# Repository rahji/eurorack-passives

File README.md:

# Passive Eurorack Non-Modules

These are small PCBs for a variety of passive Eurorack "non-modules." I designed them to be under 1" in at least one dimension¹, so they can fit neatly under a strip of 1.5" aluminum angle (architectural angle, .0625" thick) — which makes for a perfect extra row in my Halliburton cases. If you wanted to, you could probably make a 1u panel for each of them. Or put a few of them vertically behind a single 8hp 3u panel. Or put them in a mint tin. Or whatever.

The circuits are all pretty simple, use only through-hole components, and the PCBs are all essentially 1 layer². Some of them circuits are based on designs by other Eurorack folks (who likely were inspired by others). For examples, see [Yan's Patchpals](https://www.youtube.com/channel/UChDo3AJkkG8NR5XDoN58YQw), the [Doepfer A-100 DIY page](http://www.doepfer.de/DIY/a100_diy.htm), and [Synth Diy Guy](https://www.youtube.com/channel/UCaTca38SJErVLsfYkrg2R9w).

## Schematics

I've included PNG images of each of the schematics, because I hate when I find Eagle projects on GitHub and have to clone them (and open them in Eagle!) before I can get a glimpse of the schematic. 

## Assembly and BOMs

The silkscreens don't necessarily indicate which side of the board to place to the component. You can decide which side makes the most sense for you. Obviously make sure the polarity matches what the silkscreen says though.

## Panels

Labels and graphics are up to you, but I've included PDFs and AIs for each of the modules' holes. The AI files have separate layers for the hole dimensions, centered crosshairs, board dimensions, and name of the module. There's also a PDF of all of the panels on one page.

---

¹ The traces on the boards are all on the bottom layer, but practically it makes sense to have them fabricated as 2-layer boards. If you want to mill them as single-layer boards yourself, and you're willing to be creative with your soldering, you could do it.

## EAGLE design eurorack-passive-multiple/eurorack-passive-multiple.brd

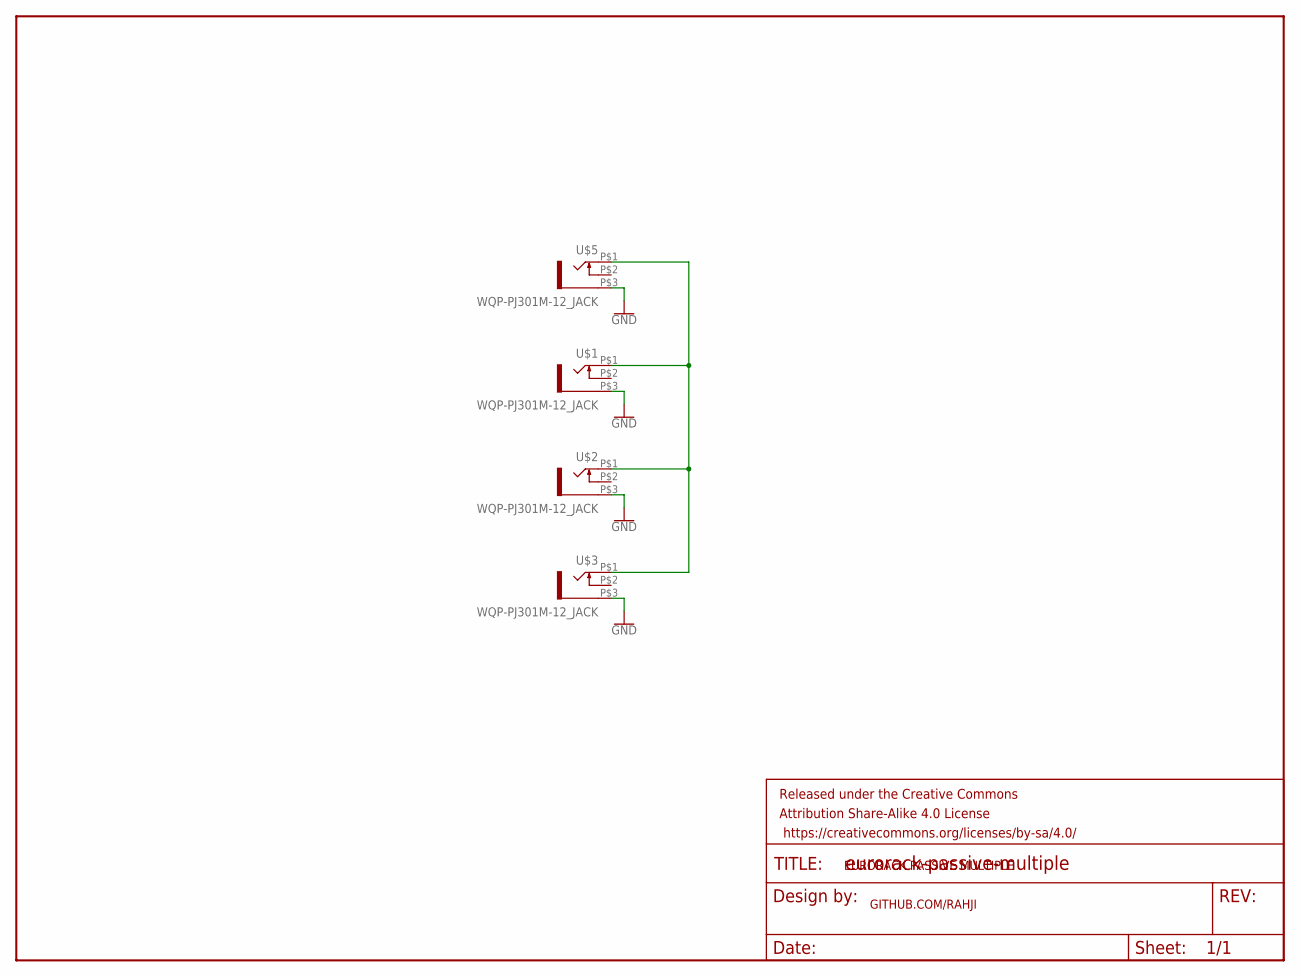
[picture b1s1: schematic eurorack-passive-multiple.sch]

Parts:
FRAME1: FRAME-LETTERNO_PACKAGE; DUMMY
U$1, U$2, U$3, U$5: WQP-PJ301M-12_JACK

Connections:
GND: U$1.P$3 (1), U$2.P$3 (1), U$3.P$3 (1), U$5.P$3 (1)
unnamed: U$1.P$1 (2), U$2.P$1 (2), U$3.P$1 (2), U$5.P$1 (2)

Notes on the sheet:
EURORACK PASSIVE MULTIPLE
GITHUB.COM/RAHJI

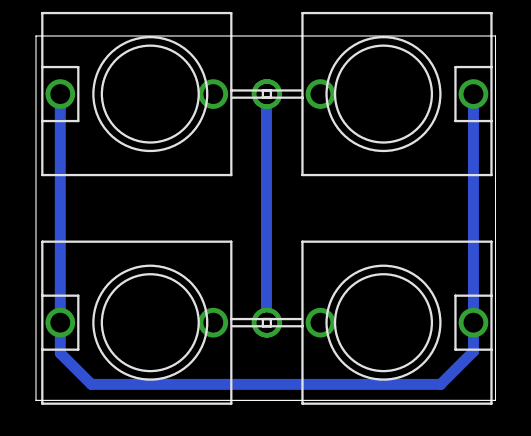
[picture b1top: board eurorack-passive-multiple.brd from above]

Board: 2 copper layers, 25.5 x 20.2 mm, 5 parts (0 on the bottom side), 2 nets.

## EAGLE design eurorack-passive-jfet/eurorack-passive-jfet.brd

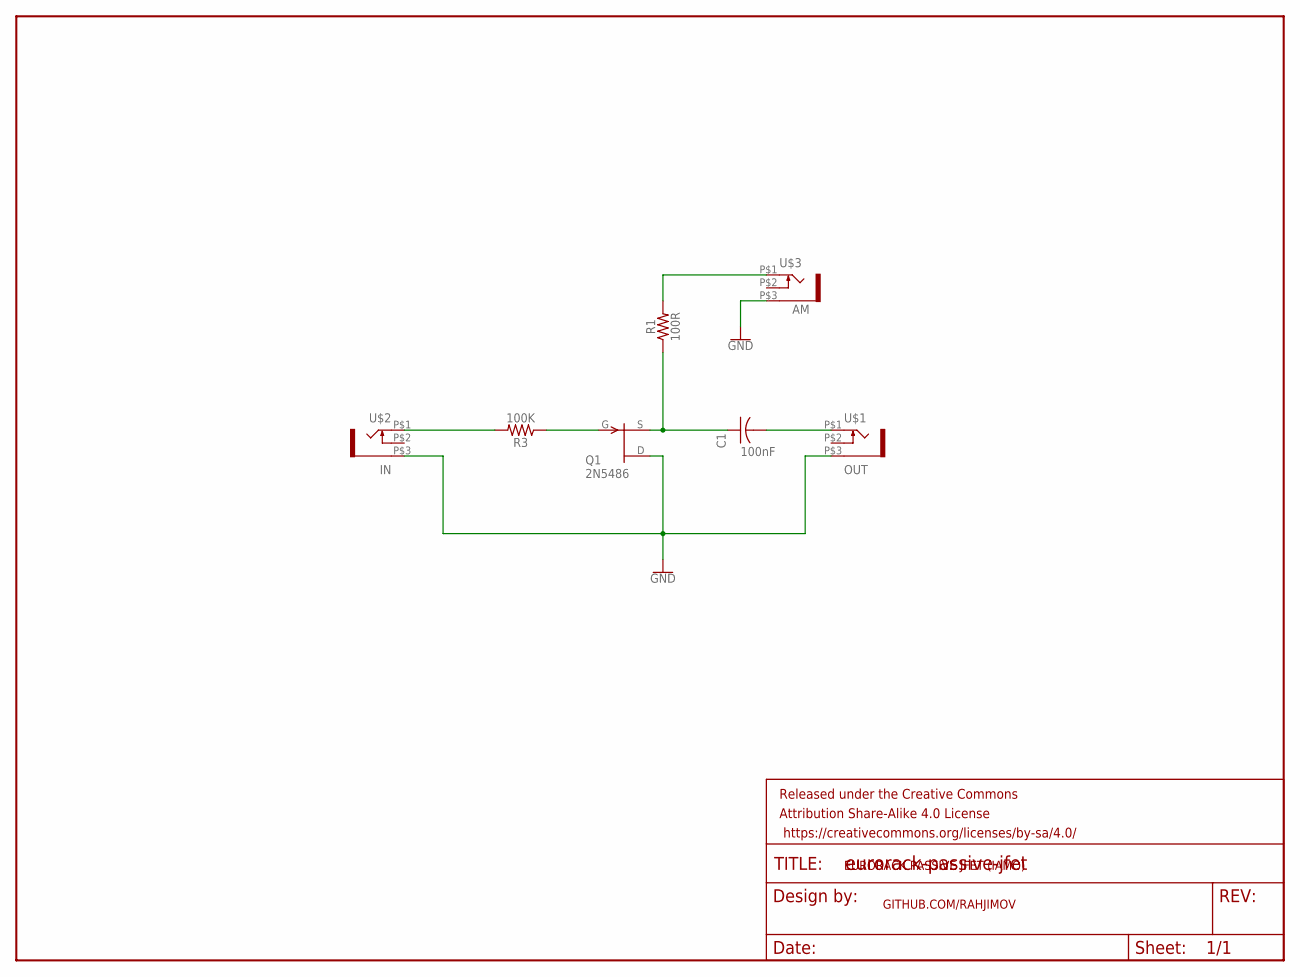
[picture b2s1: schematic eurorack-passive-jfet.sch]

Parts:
C1: 100nF; C025-025X050
FRAME1: FRAME-LETTERNO_PACKAGE; DUMMY
Q1: 2N5486; TO92-
R1: 100R; AXIAL-0.3
R3: 100K; AXIAL-0.3
U$1, U$3: OUT; WQP-PJ301M-12_JACK
U$2: IN; WQP-PJ301M-12_JACK

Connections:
GND: Q1.3 (D), U$1.P$3 (1), U$2.P$3 (1), U$3.P$3 (1)
unnamed: R1.P$2 (2), U$3.P$1 (2)
unnamed: C1.1, Q1.2 (S), R1.P$1 (1)
unnamed: C1.2, U$1.P$1 (2)
unnamed: R3.P$2 (2), U$2.P$1 (2)
unnamed: Q1.1 (G), R3.P$1 (1)

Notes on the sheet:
EURORACK PASSIVE JFET (IAMO)
GITHUB.COM/RAHJIMOV
100nF

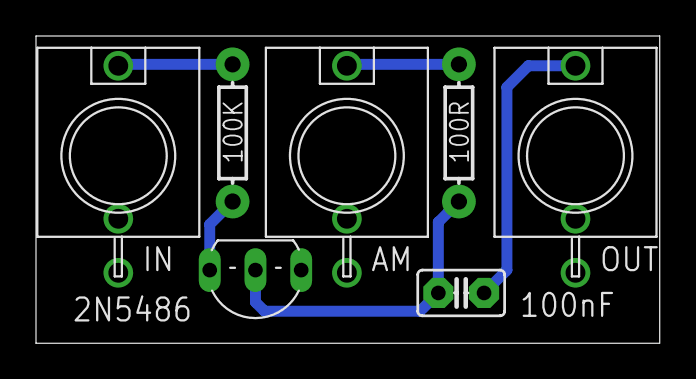
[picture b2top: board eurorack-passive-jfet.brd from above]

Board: 2 copper layers, 34.7 x 17.1 mm, 8 parts (0 on the bottom side), 6 nets.

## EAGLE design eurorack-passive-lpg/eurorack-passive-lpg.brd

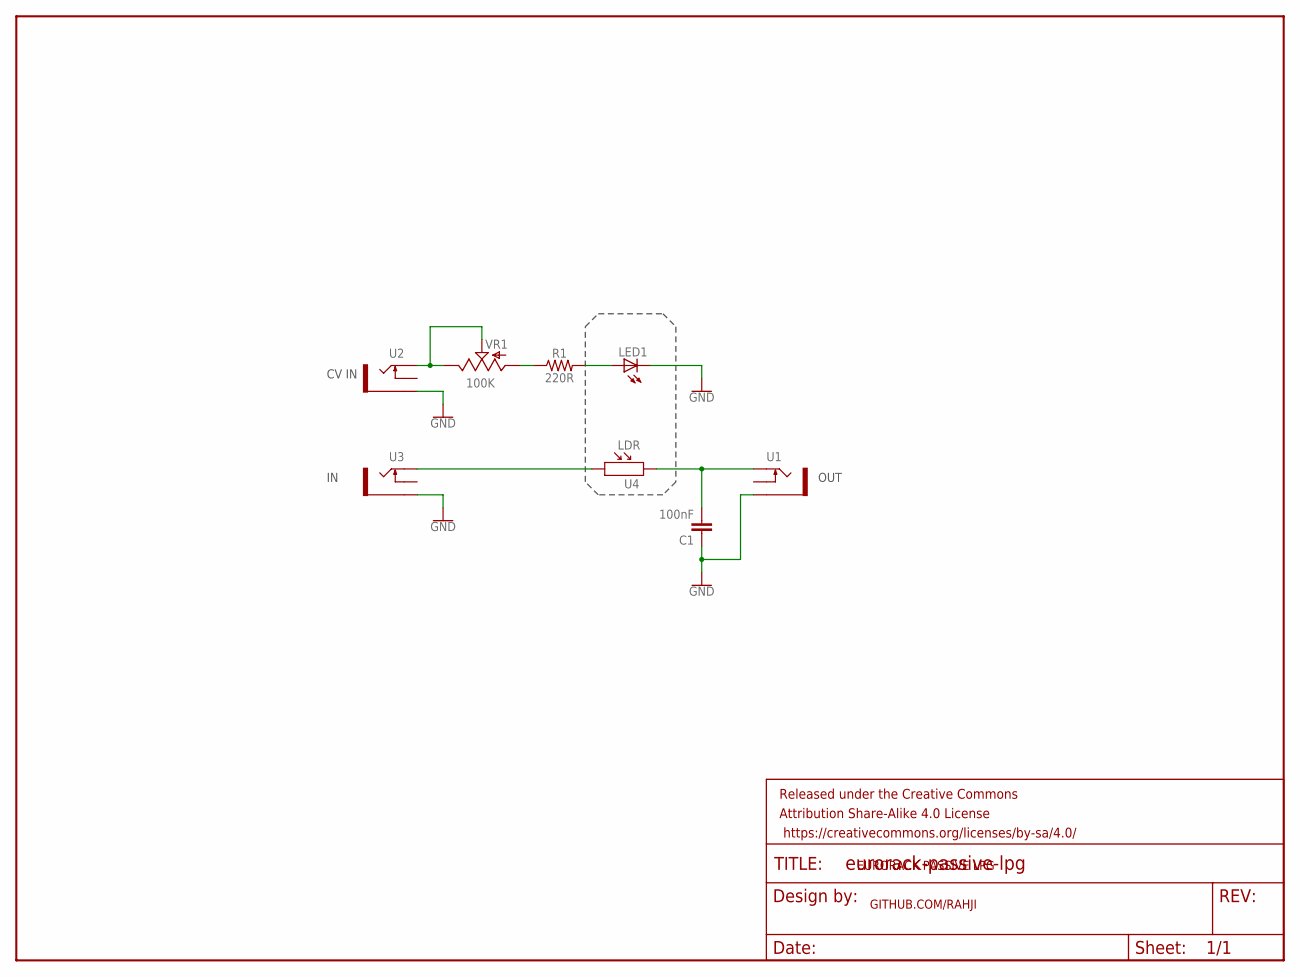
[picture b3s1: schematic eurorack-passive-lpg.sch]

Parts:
C1: 100nF; CAP-PTH-2.54
FRAME1: FRAME-LETTERNO_PACKAGE; DUMMY
LED1: LED5MM
R1: 220R; AXIAL-0.3
U1: OUT; WQP-PJ301M-12_JACK
U2: CV IN; WQP-PJ301M-12_JACK
U3: IN; WQP-PJ301M-12_JACK
U4: LDR; SNR2-3.0
VR1: 100K; 9MM_SNAP-IN_POT

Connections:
GND: C1.1, LED1.K (C), U1.P$3_SLEEVE (SLEEVE), U2.P$3_SLEEVE (SLEEVE), U3.P$3_SLEEVE (SLEEVE)
unnamed: U2.P$1_TIP (TIP), VR1.2 (S), VR1.3 (E)
unnamed: R1.P$1 (1), VR1.1 (A)
unnamed: U3.P$1_TIP (TIP), U4.1
unnamed: LED1.A, R1.P$2 (2)
unnamed: C1.2, U1.P$1_TIP (TIP), U4.2

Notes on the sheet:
CV IN
OUT
EURORACK PASSIVE LPG
GITHUB.COM/RAHJI

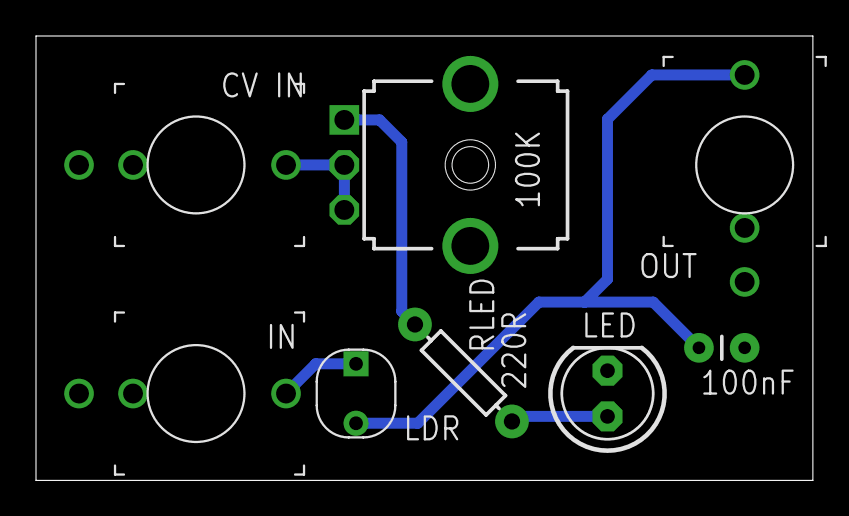
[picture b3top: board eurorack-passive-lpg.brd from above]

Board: 2 copper layers, 43.2 x 24.7 mm, 9 parts (0 on the bottom side), 6 nets.

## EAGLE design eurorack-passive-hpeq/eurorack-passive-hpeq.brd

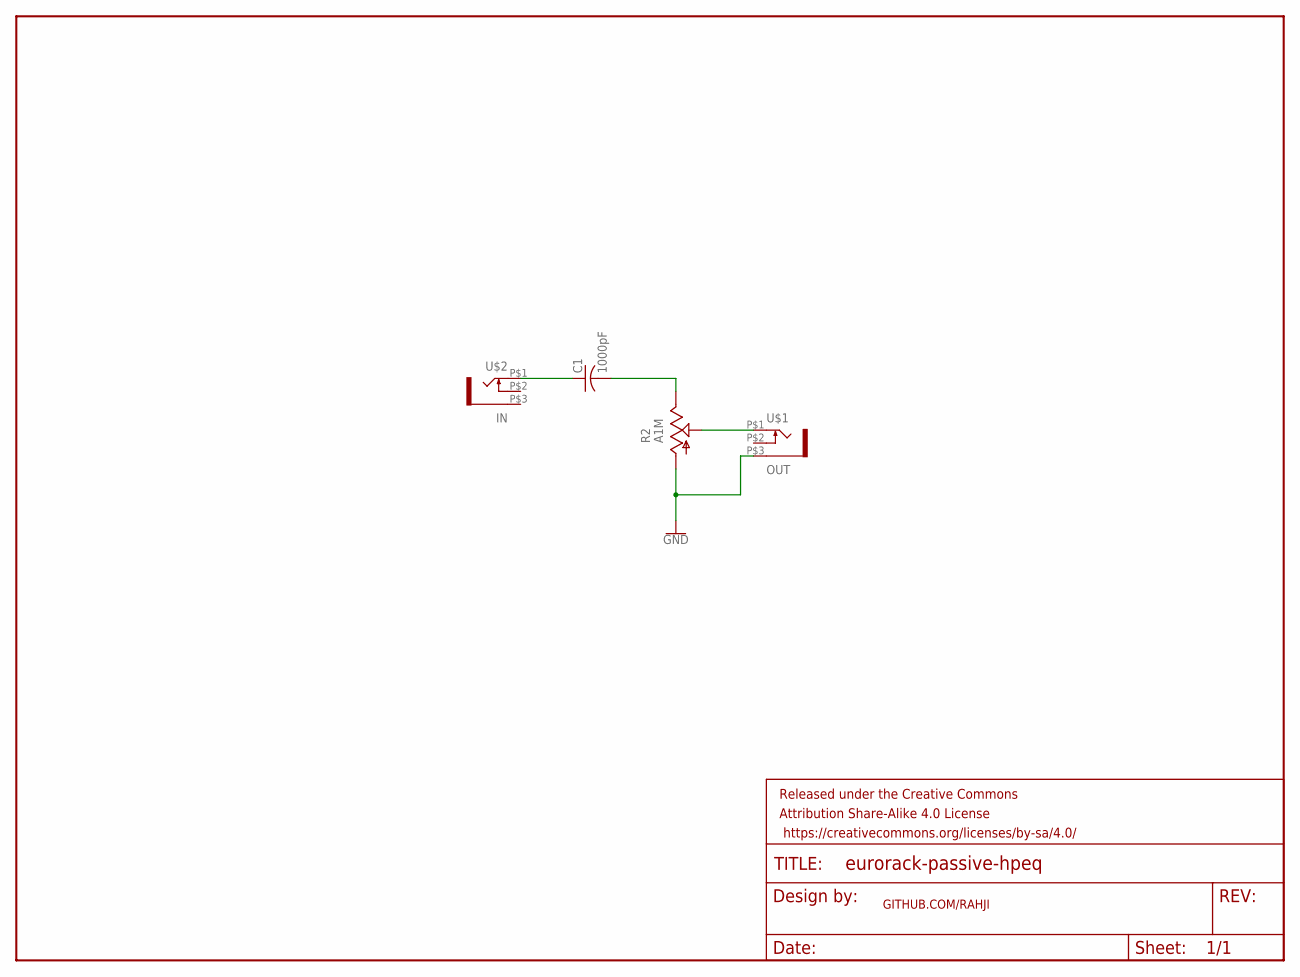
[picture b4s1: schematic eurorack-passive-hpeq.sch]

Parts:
C1: 1000pF; C025-025X050
FRAME1: FRAME-LETTERNO_PACKAGE; DUMMY
R2: A1M; EVUF
U$1: OUT; WQP-PJ301M-12_JACK
U$2: IN; WQP-PJ301M-12_JACK

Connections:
GND: R2.1 (A), U$1.P$3 (1)
unnamed: C1.1, U$2.P$1 (2)
unnamed: C1.2, R2.3 (E)
unnamed: R2.2 (S), U$1.P$1 (2)

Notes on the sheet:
GITHUB.COM/RAHJI

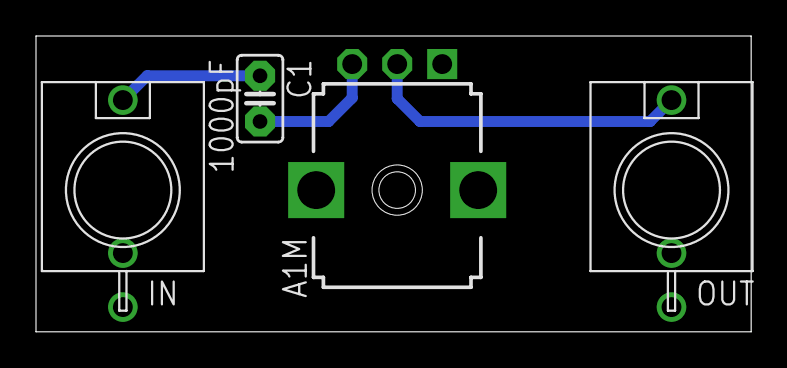
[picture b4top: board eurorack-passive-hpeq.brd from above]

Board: 2 copper layers, 39.7 x 16.4 mm, 5 parts (0 on the bottom side), 4 nets.

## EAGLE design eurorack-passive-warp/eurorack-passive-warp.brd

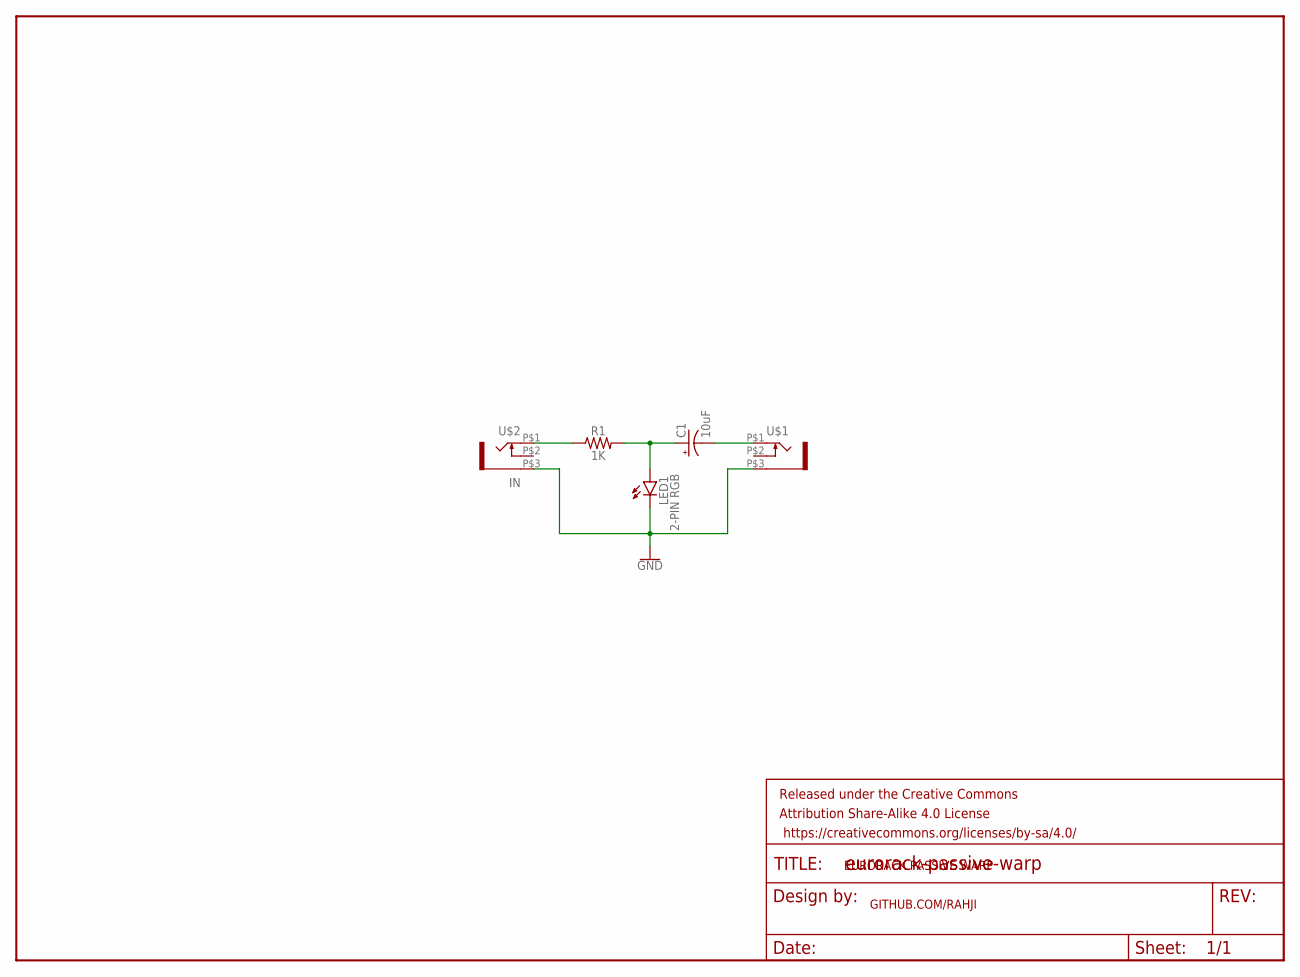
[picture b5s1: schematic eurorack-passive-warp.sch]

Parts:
C1: 10uF; CPOL-RADIAL-2.5MM-5MM
FRAME1: FRAME-LETTERNO_PACKAGE; DUMMY
LED1: 2-PIN RGB; LED5MM
R1: 1K; AXIAL-0.3
U$1: OUT; WQP-PJ301M-12_JACK
U$2: IN; WQP-PJ301M-12_JACK

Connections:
GND: LED1.K (C), U$1.P$3 (1), U$2.P$3 (1)
unnamed: R1.P$1 (1), U$2.P$1 (2)
unnamed: C1.1 (+), LED1.A, R1.P$2 (2)
unnamed: C1.2 (-), U$1.P$1 (2)

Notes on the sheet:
EURORACK PASSIVE WARP
GITHUB.COM/RAHJI

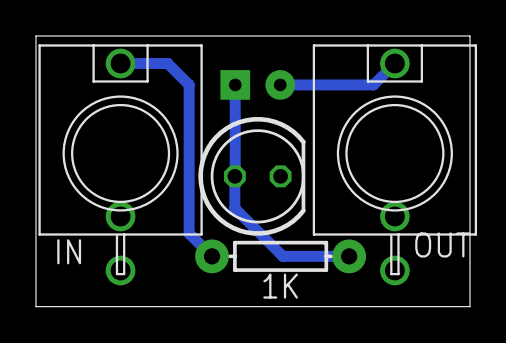
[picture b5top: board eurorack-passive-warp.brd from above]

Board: 2 copper layers, 24.1 x 15.0 mm, 6 parts (1 on the bottom side), 4 nets.

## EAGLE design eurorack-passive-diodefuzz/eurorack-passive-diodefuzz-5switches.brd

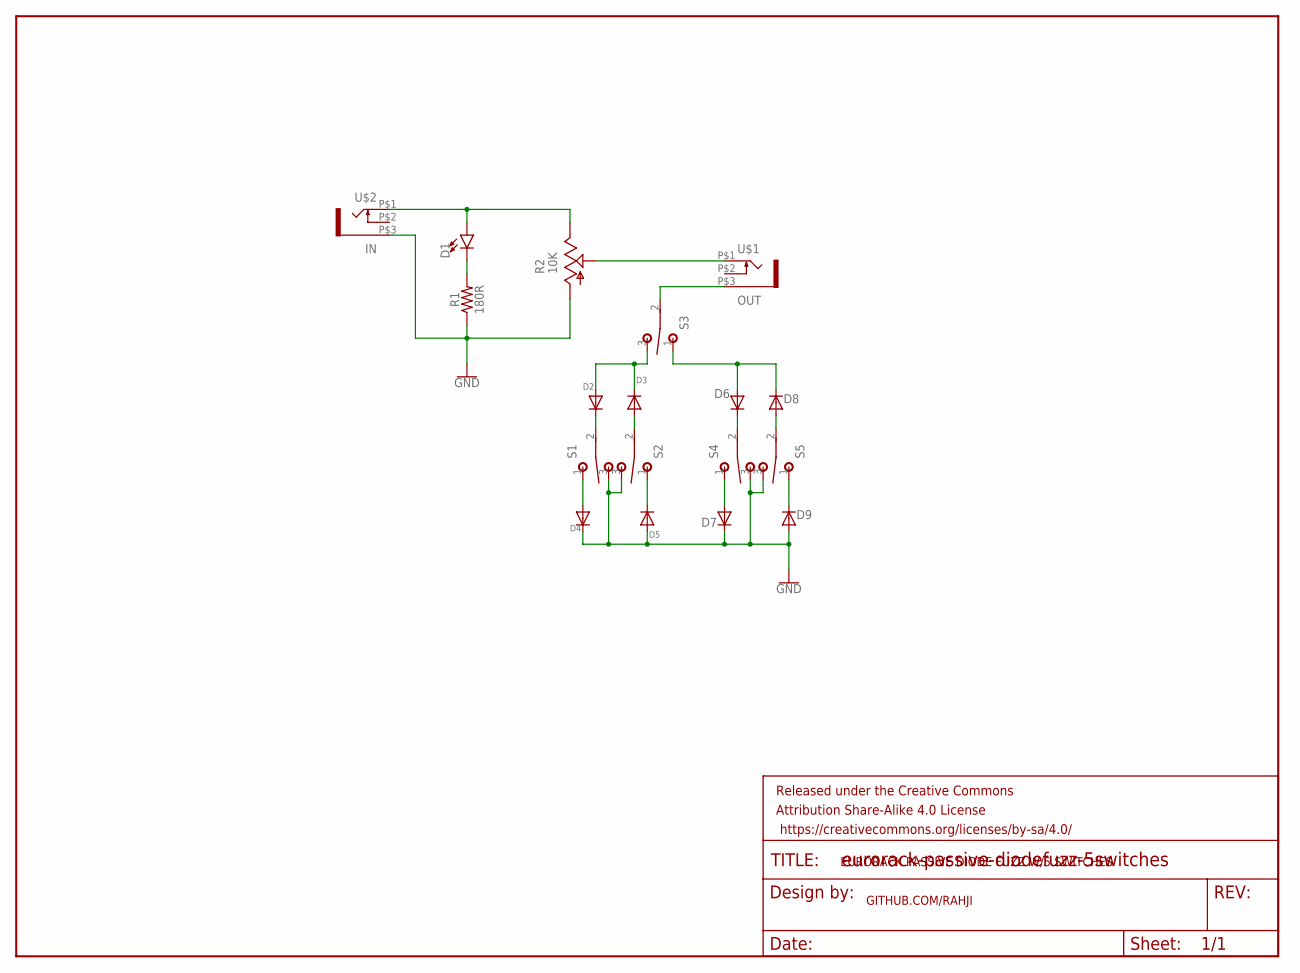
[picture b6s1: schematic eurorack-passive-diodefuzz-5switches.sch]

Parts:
D1: LED5MM; LED_5MM
D2, D3, D4, D5, D6, D7, D8, D9: VERTICAL_DIODE; C1702-05
FRAME1: FRAME-LETTERNO_PACKAGE; DUMMY
R1: 180R; AXIAL-0.3
R2: 10K; EVUF
S1, S2, S3, S4, S5: SPDT; M9040P
U$1: OUT; WQP-PJ301M-12_JACK
U$2: IN; WQP-PJ301M-12_JACK

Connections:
GND: D4.C, D5.A, D7.C, D9.A, R1.P$1 (1), R2.1 (A), S1.3 (S), S2.3 (S), S4.3 (S), S5.3 (S), U$2.P$3 (1)
unnamed: D1.A, R2.3 (E), U$2.P$1 (2)
unnamed: D1.K (C), R1.P$2 (2)
unnamed: R2.2 (S), U$1.P$1 (2)
unnamed: S3.2, U$1.P$3 (1)
unnamed: D2.A, D3.C, S3.3 (S)
unnamed: D2.C, S1.2
unnamed: D3.A, S2.2
unnamed: D4.A, S1.1 (O)
unnamed: D6.C, S4.2
unnamed: D5.C, S2.1 (O)
unnamed: D8.A, S5.2
unnamed: D6.A, D8.C, S3.1 (O)
unnamed: D7.A, S4.1 (O)
unnamed: D9.C, S5.1 (O)

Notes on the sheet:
EURORACK PASSIVE DIODE FUZZ W/5 SWITCHES
GITHUB.COM/RAHJI

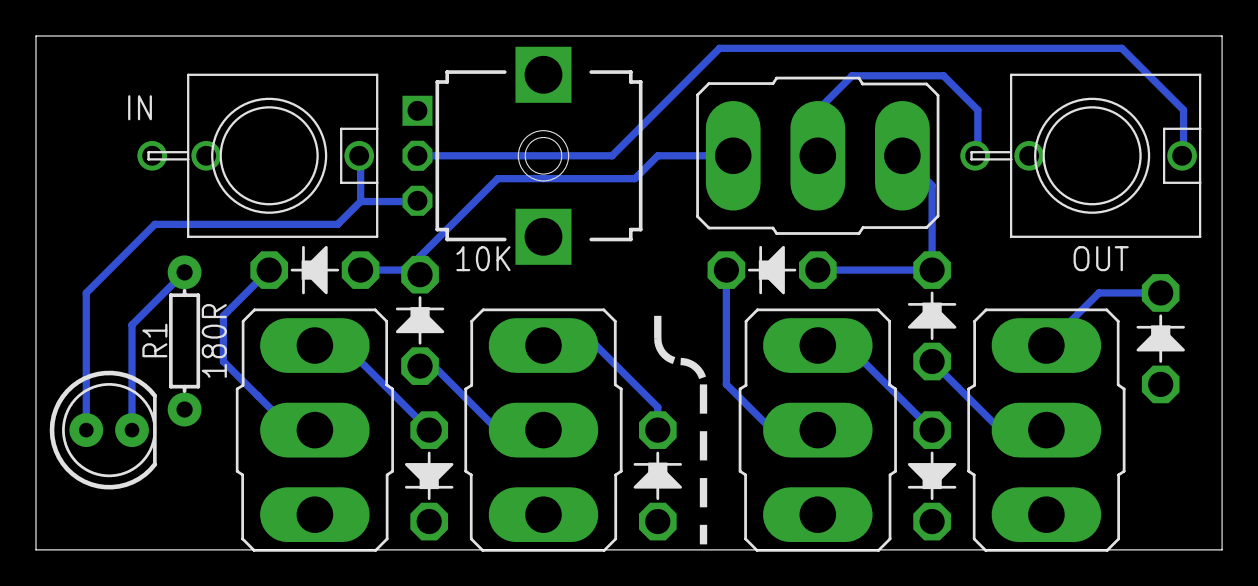
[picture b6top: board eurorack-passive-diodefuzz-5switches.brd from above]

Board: 2 copper layers, 65.9 x 28.5 mm, 19 parts (0 on the bottom side), 15 nets.

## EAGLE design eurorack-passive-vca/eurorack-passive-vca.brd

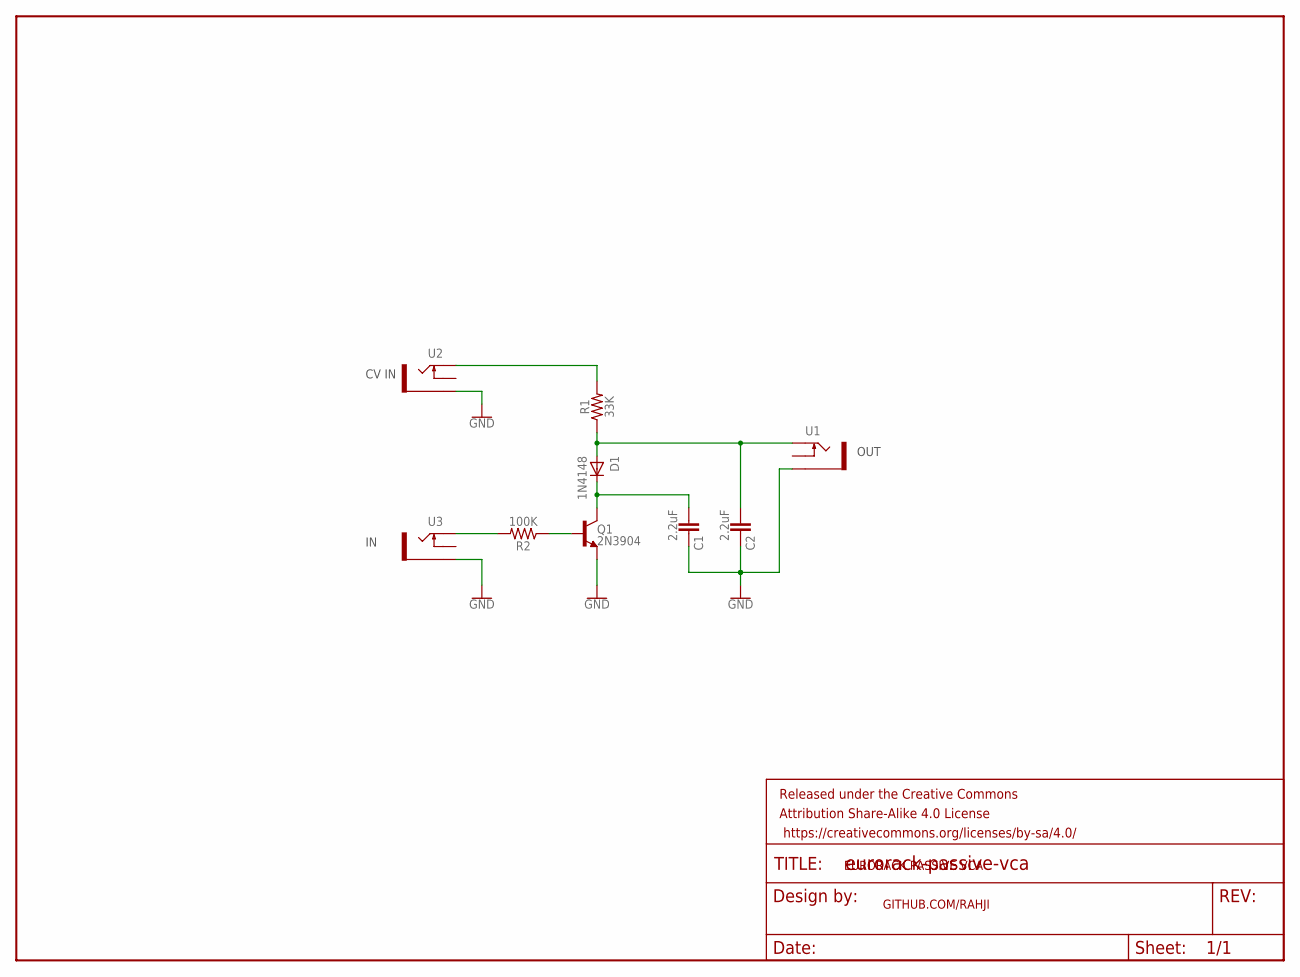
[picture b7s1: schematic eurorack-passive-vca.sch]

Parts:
C1, C2: 2.2uF; CAP-PTH-2.54
D1: 1N4148; DO-1N4148
FRAME1: FRAME-LETTERNO_PACKAGE; DUMMY
Q1: 2N3904; TO-92
R1: 33K; AXIAL-0.3
R2: 100K; AXIAL-0.3
U1: OUT; WQP-PJ301M-12_JACK
U2: CV IN; WQP-PJ301M-12_JACK
U3: IN; WQP-PJ301M-12_JACK

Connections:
GND: C1.1, C2.1, Q1.1 (E), U1.P$3_SLEEVE (SLEEVE), U2.P$3_SLEEVE (SLEEVE), U3.P$3_SLEEVE (SLEEVE)
unnamed: R1.P$2 (2), U2.P$1_TIP (TIP)
unnamed: C2.2, D1.A, R1.P$1 (1), U1.P$1_TIP (TIP)
unnamed: R2.P$2 (2), U3.P$1_TIP (TIP)
unnamed: Q1.2 (B), R2.P$1 (1)
unnamed: C1.2, D1.C, Q1.3 (C)

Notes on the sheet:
CV IN
OUT
EURORACK PASSIVE VCA
GITHUB.COM/RAHJI

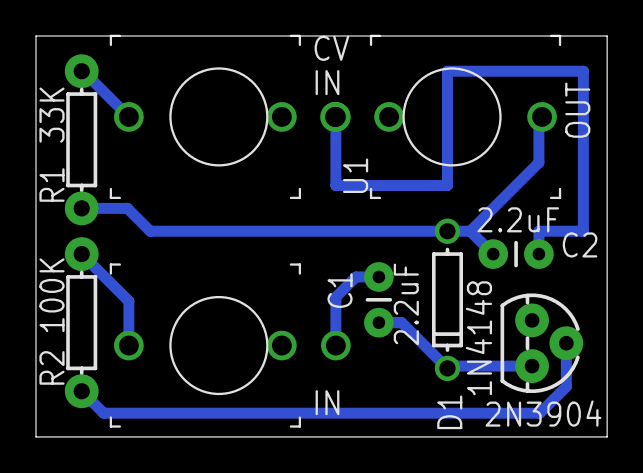
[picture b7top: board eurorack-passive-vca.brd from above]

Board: 2 copper layers, 31.7 x 22.3 mm, 10 parts (0 on the bottom side), 6 nets.

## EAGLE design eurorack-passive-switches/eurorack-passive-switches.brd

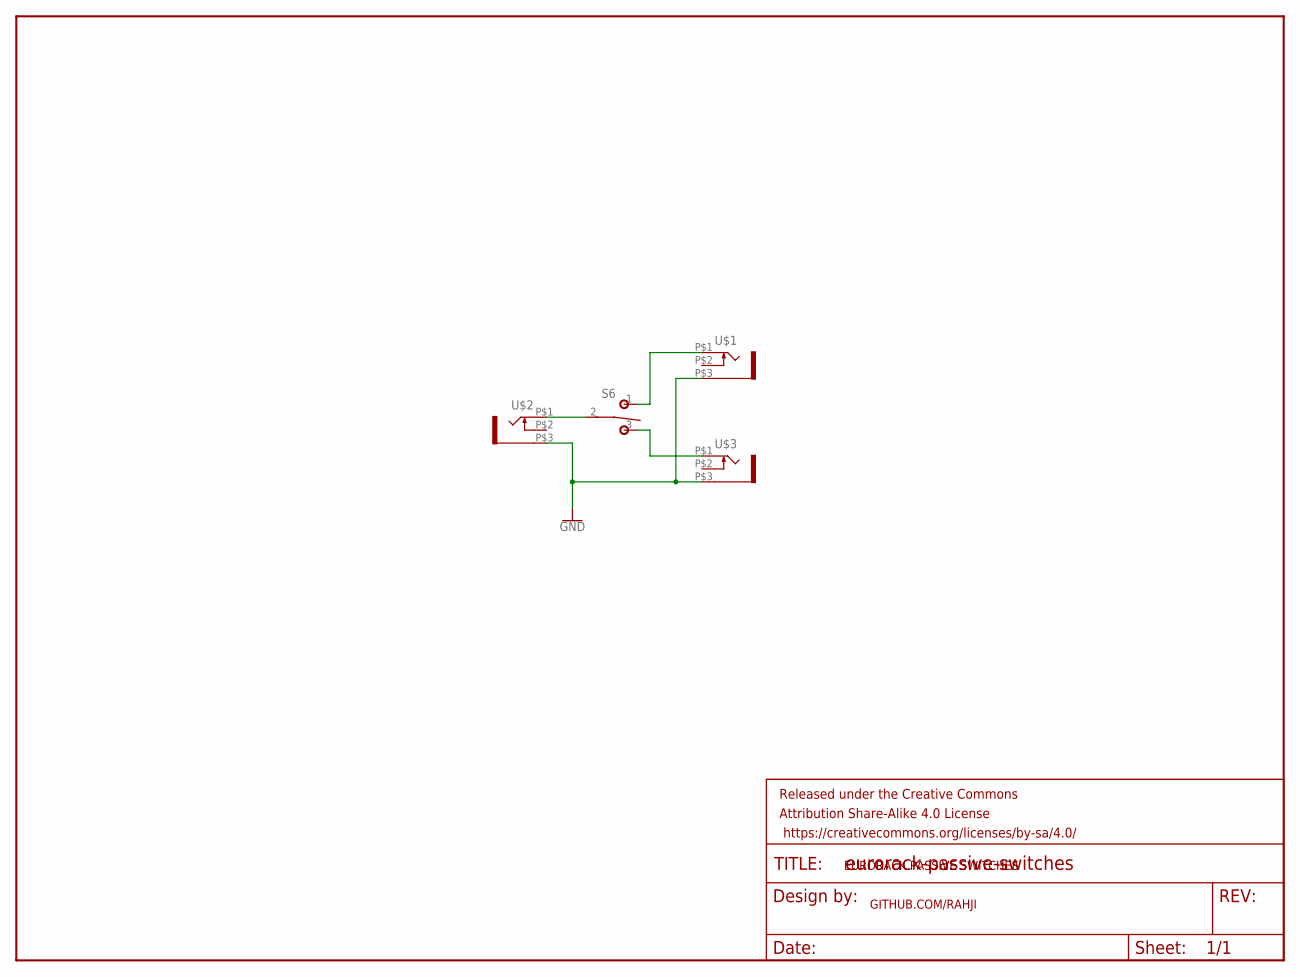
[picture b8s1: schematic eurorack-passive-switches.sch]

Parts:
FRAME1: FRAME-LETTERNO_PACKAGE; DUMMY
S6: SPDT; M9040P
U$1, U$3: OUT; WQP-PJ301M-12_JACK
U$2: IN; WQP-PJ301M-12_JACK

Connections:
GND: U$1.P$3 (1), U$2.P$3 (1), U$3.P$3 (1)
unnamed: S6.2, U$2.P$1 (2)
unnamed: S6.1 (O), U$1.P$1 (2)
unnamed: S6.3 (S), U$3.P$1 (2)

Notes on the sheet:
EURORACK PASSIVE SWITCHES
GITHUB.COM/RAHJI

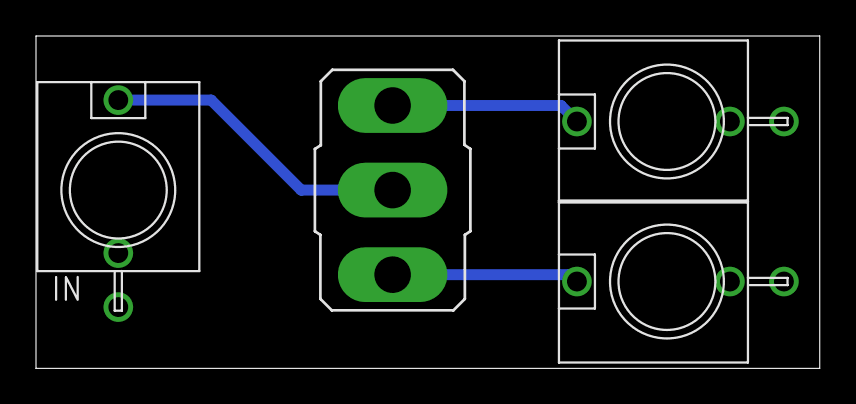
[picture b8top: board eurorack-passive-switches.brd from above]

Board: 2 copper layers, 43.5 x 18.5 mm, 5 parts (0 on the bottom side), 4 nets.

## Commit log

2021-01-29 Adding files that were just sent to OSH Park
2021-02-01 Added PNGs of schematics
    I hate when people make me open the SCH file in Eagle just to see the schematic.
2021-02-01 Renamed diodefuzz eagle files
2021-02-06 Added AI and PDF files for each panel
2021-02-07 joined dimension lines on warp panel drawings
    ¯\_(ツ)_/¯
2021-07-09 Removed diode fuzz

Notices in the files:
parts and their libraries:
SparkFun-LED: Licensing: Creative Commons ShareAlike 4.0 International - https://creativecommons.org/licenses/by-sa/4.0
SparkFun-Aesthetics: Released under the Creative Commons Attribution Share-Alike 4.0 License
SparkFun-Aesthetics: https://creativecommons.org/licenses/by-sa/4.0
